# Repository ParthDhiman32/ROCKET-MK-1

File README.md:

# ROCKET-MK-1
This is a fixed fin experimental rocket built for the purpose of collecting useful flight data and also showcasing high level engineering skills 

# Project Theory
For this project I will be designing simulating and fabricating a fixed fin rocket from scratch using the rocket motor as the starting point for calculating all other parameteres like the diameter of the main body tube and the nosecone length and gemoetry and the fin geometry 
the rocket motor's impulse also dictates the maximum weight of the rocket as the thrust to weight ratio should be a minimum of 5:1 considering the resistive forces acting uptom the rocket like the drag from the rocket's weight and also the aerodynamic drag which is the factor which we need to optimize our rocket for we need a very aeroynamically optimized body for the rocket to be able to cut through the air smoothly with minimum drag and deviation 
the rocket should launch perfectly vertical and shall not deviate more then 1-5 degrees from the horizontal from the launch rail The rockst's fins should be optimized to suffer from no Aerosynamic fin flutter.
Aerodynamic Fin Flutter is a destructive process in which the rocket's wings bend under stress and strain as they are travelling at very high speed (upwards of Mach 0.5) for this rocket the fins start to resonate because of the external force which the air provides for stabilizing the rocket but in this special case the air starts to resonate the fin and the fin starts to vibrate from it's mean position which and hench resonate which exposes the fin to much more flutter than it can possibly handel and hence breaks apart.
to avoid this we must use a lightweight material with the highest young's modulus which provided maximum stiffness and negligible strain 
Materials such as Fiberglass, carbon fiber, 3D printed CF-Nylong provide high stiffness ideal for optimizing the fins from restraining from fin flutter 

# Starting parameteres 
Now let's start talking about numbers and actual starting parameteres for the rocket

**Rocket Motor**
Now there are many different classes of rockets ranging from class micro and A going through E F G H I J K L and reaching to upwards of AJ
However for model rocketry we generally use from class D to the largest one S 
These rocket motor classes are alphabetical and classified by Magnitude of impulse they can produce

For my Rocket i will be using a F class rocket motor producing a Max Impulse of 67Ns
I will be using the rocketeers F57 motor 

This motor has 
Diameter of 29mm <br>
Weight = 177g (wet mass)<br>
Burn time = 1.14s<br>

This motor's casing is made from aerospace grade Aluminium 
Nozzel is manufactured out of graphite 
and all very high quality materials are used in this entire rocket motor assembly

# Rocket dimensions
Thr rocket's exact dimenstions are yet to be simulated and found out but for now we have these as the starting points
Rocket length = 650 ~ 975mm<br>
Main Body tube length = 455 ~ 650mm<br>
Avaionics bay length = 120 ~ 165mm<br>
Nose cone length 195 ~ 325mm<br>
Nose cone profile = Ogive (3:1)<br>
Outter tube diameter = 65mm<br>
Target liftoff mass = 500~600 grams<br>
Static stability margin = 1~1.5 cal<br>
3-4 Fixed fins - Trapezoid shape <br>

# Mission Objective 
Apogee > 100 Meteres<br>
Mantain Stable vertical flight <br>
All Flight Data logged successfully <br>
Working Telementry<br>
Rocket Recovery <br>

# Work Flow
Firstly the rough design will be simulated in Open rocket and the simulation data will be used for finding the perfect rocket profile values 

Then the entire rocket will be imported inside fusion 360 and the launch mechanism the launch rail and the cross section of the rocket and the fin joint mechanism and then avaionics bay will also be shown in the horizontal cross section of the rocket 

Then i will prototype the avaionics bay on breadboards and design the rough data logging program and logic This will be a time consuming process 

After this i will convert the entire avaionics circitry into a PCB which will be as small as possible and Be mounted vertically inside the Avaionics bay 

then i will also create the remote ignition and most importantly the ground telementry station which will comminucate via LoRa

After that I will work on creating proper joining mechanisms for the rocket and the final circuitry 

Then i will finalize the rocket design and start ordering parts for it's fabrication and assembly 

Then carefully assemble each and every part and test for any errors 

then calculate the Moment of inertia find the actual center of mass and center of pressure 

Simulate and perfect again in Openrocket 

Then create an even more accurate model in matlab simulink 

Test and analyze again

Then a dry run 

The Actual Flight 

# Avionics <br>
I will be using these main sensors for the avaionics (rough idea)<br>
ESP32 S3 Wroom-1<br>
BMI270 - 3 axis acceleration + 3 axis gyroscope <br>
ADXL377 - 3 axis high G accelerometer<br>
Barometric pressure sensor - altitude measurement<br>
DS3231 - Time stamping<br>
Sd card module - data logging <br>
loRa - Telementry <br>
2 Li-ion battries for Power<br>
umbilical cord connector = communication of Remote ignition from ground station to the rocket and the launch rail <br>

# Launch rail<br>
The launch rail will be made out of 2020 aluminium extrusion with arms which will hold the rocket in place (cool factor) and it will use a Rail button<br>

# OpenRocket model 
*1st Iteration estimates*

Apogee = 285m <br>
Max speed = Mach 0.245<br>
Max acceleration = 83.3m/s^2<br>

*2nd Iteration estimates*

Apogee = 281m<br>
Max speed = Mach 0.240<br>
Max acceleration = 84.6m/s^2 <br>

This version has a more agressive look and also has a much higher stability caliber(2.19Cal) then the last iteration.<br>
I upgraded from a 2020 Aluminium extrusion because a 1010 aluminium extrusion was not very easily available in india.<br>

# Render in fusion360

# Avionics sled V1
<br>
<br>
<br>

# Remote ignition system 

# How to actually build the rocket 
1. Download this repo on your computer
2. Buy all the materials required for the rocket as listed in the BOM
3. Start by taking the carboard main body tube
4. 3D print the nosecone
5. cut the fins out of balsa wood and make insitions inside of the cardboard bodytube for fitting the fins
6. Also cut out the centering rings from the rocket's main body tube
7. Take wood glue and apply it on the centering rings and then slide then at exact depth as mentioned inside the openrocket rocket's model
8. after the centering rings are applied do the same and glue the fins inisde the rocket's main body tube
9. Take the rocket motor and slide it inside the centering rings from the bottom
10. Take the 3d printed nosecone and see if it fits from the top properly
11. make sure it fits tightly enough that it can slip out with force but not when you're lifting the rocket by holding the nosecone
12. Apply tape around the circumfrence of the nose cone's neck if required to a tighter fit
13. after this you may spray a thin layer of primer on the cardboard tube and then spray paint it black
14. Now comes the Avionics
15. Get the Avionics pcb fabricated
16. Solder all the avionics components as shows in the kicad pcb schematics
17. After getting the pcb ready
18. build the ground station on a perf board or a breadboard
19. power up the pcb and the ground station
20. make sure to connect the LoRa antennas before powering on the pcb else it it may fry itself
21. Upload the codes of ther Avionics sender and ground station recuiever respectively
22. Download Serial Studios and open the serial studio profile provided inside the repo
23. Connect the ground station and you should see the serial studio dashboard working
24. After that 3D print the Avionics sled for the Avionics PCB
25. Connect the avionics on the sled via proper M3 screws
26. TAke the sled and slide it inside the rocket's main body tube and then close the nosecone
27. Make sure that the rocket Telementry is working properly
28. Drill a small hole isnide the cardboard tube at the angle bisector between two of the fur fins and connect the rail button
29. Take the 6 Feet 2020 Aluminium extrusion
30. Put it firmly on a tripod stand or a dedicated Launch pad for a model rocket
31. Get the Ignition reciever PCB fabriacted and solder all the components
32. 3D print the acse for the PCB
33. Connecte a 12V Lead acid battery to the ignition bat connector also power the ignition reciever staion with 5V from a smaller battery
34. Connect the igniton plug inside the rocket's motor
35. Now staand atleast 10 meters away from the launch site (make sure you have all the certifications reqired to launch a model rocket according to your local jurisdiction)
36. Load up the Serial studio dashboard
37. Press the launch button o the ground station reciever
38. Rocket launches (hopefully)

# BOM 

| Category | Item Description | Manufacturer / Serial No. / Part Number | Qty | Est. Unit Price (USD) | Primary Vendor / Website |
| :--- | :--- | :--- | :---: | :---: | :--- |
| **Avionics & Processing** | ESP32-S3 Dev Board | Espressif / ESP32-S3-DevKitC-1 | 2 | \$6.50 | [DigiKey](https://www.digikey.com) |
| **Avionics & Processing** | LoRa Transceiver Module (915MHz/433MHz) | HopeRF / RFM95W-915S2 | 2 | \$4.80 | [Adafruit](https://www.adafruit.com) |
| **Avionics & Processing** | 50Ω SMA Male Rubber Duck Antenna | Generic / ANT-SMA-915-01 | 2 | \$2.00 | [Amazon](https://www.amazon.com) |
| **Sensors** | 6-DOF IMU (Gyroscope + Accelerometer) | Bosch / BMI270-BRK | 1 | \$5.50 | [Pimoroni](https://shop.pimoroni.com) |
| **Sensors** | High-G Accelerometer Module | Analog Devices / ADXL345-BRK | 1 | \$4.20 | [SparkFun](https://www.sparkfun.com) |
| **Sensors** | Barometric Pressure & Altitude Sensor | Bosch / BMP280-BRK | 1 | \$3.50 | [Adafruit](https://www.adafruit.com) |
| **Sensors** | 3-Axis Digital Compass / Magnetometer | QST / QMC5883L-MOD | 1 | \$2.50 | [AliExpress](https://www.aliexpress.com) |
| **Sensors** | GPS Receiver Module w/ Ceramic Antenna | u-blox / NEO-6M-0-001 | 1 | \$11.00 | [Amazon](https://www.amazon.com) |
| **Sensors** | Real-Time Clock (RTC) Module | Maxim / DS3231-RTC-MOD | 1 | \$2.80 | [Adafruit](https://www.adafruit.com) |
| **Data & Interfaces** | MicroSD Card Breakout Module (SPI) | Adafruit / ID-254 | 1 | \$1.80 | [Adafruit](https://www.adafruit.com) |
| **Data & Interfaces** | Class 10 MicroSD Card (16GB) | SanDisk / SDSQUNC-016G-GN6MA | 1 | \$7.00 | [Amazon](https://www.amazon.com) |
| **Data & Interfaces** | USB-C High-Speed Data Cable (1m) | Anker / A81E1011 | 2 | \$3.00 | [Monoprice](https://www.monoprice.com) |
| **Power & Passives** | 3.7V 1S LiPo Battery (1000mAh 25C) | Turnigy / N1000.1S.25 | 1 | \$6.50 | [HobbyKing](https://hobbyking.com) |
| **Power & Passives** | TP4056 LiPo Charge/Protection Module | Micro-USB TP4056-PROT | 1 | \$0.80 | [AliExpress](https://www.aliexpress.com) |
| **Power & Passives** | 3.3V Low Dropout LDO Regulator | Advanced Monolithic / AMS1117-3.3 | 2 | \$0.40 | [DigiKey](https://www.digikey.com) |
| **Power & Passives** | Ceramic Capacitor 0.1uF 50V (0805/DIP) | KEMET / C0805C104K5RACTU | 10 | \$0.05 | [Mouser](https://www.mouser.com) |
| **Power & Passives** | Tantalum Capacitor 10uF 16V | AVX / TAJB106K016RNJ | 4 | \$0.25 | [Mouser](https://www.mouser.com) |
| **Power & Passives** | Resistor Kit (2.2kΩ, 4.7kΩ, 10kΩ, 220Ω) | Yageo / MFR-25FRF52 Series | 1 set | \$5.00 | [Amazon](https://www.amazon.com) |
| **Airframe & Hardware** | Spiral Wound Cardboard Tube (62mm ID) | Apogee Components / Tubing-62mm | 1m | \$12.00 | [Apogee Components](https://www.apogeerockets.com) |
| **Airframe & Hardware** | Airframe Coupler Tube (62mm ID Fit) | Apogee Components / Coupler-62mm | 1 | \$5.00 | [Apogee Components](https://www.apogeerockets.com) |
| **Airframe & Hardware** | PETG Filament 1.75mm (Sled Printing) | Prusametrix / PETG-JET-BLACK | 1 | \$22.00 | [Prusa Research](https://www.prusa3d.com) |
| **Airframe & Hardware** | M4 Threaded Rods Stainless Steel (300mm) | McMaster-Carr / 98846A029 | 2 | \$2.50 | [McMaster-Carr](https://www.mcmaster.com) |
| **Airframe & Hardware** | M3 x 5mm x 4.2mm Brass Heat-Set Inserts | McMaster-Carr / 94180A331 | 8 | \$0.20 | [McMaster-Carr](https://www.mcmaster.com) |
| **Airframe & Hardware** | Birch Plywood Centering Rings (62mm OD) | Custom Laser / CR-62-3MM | 3 | \$2.00 | Local Laser Cutting |
| **GCS & Countdown** | Heavy Duty Toggle Switch w/ Safety Cover | Gardner Bender / GSW-11 | 5 | \$1.50 | [Amazon](https://www.amazon.com) |
| **GCS & Countdown** | Momentary Red E-Stop Push Button Switch | Ideal / Push-Red-Mushroom-22mm | 1 | \$3.50 | [AliExpress](https://www.aliexpress.com) |
| **GCS & Countdown** | PAM8403 Audio Amplifier Module | Mini PAM8403-2CH-3W | 1 | \$1.20 | [AliExpress](https://www.aliexpress.com) |
| **GCS & Countdown** | 8Ω 2W Mini Speaker Module | CUI Devices / CMS-151185-078SP | 1 | \$1.50 | [DigiKey](https://www.digikey.com) |
| **GCS & Countdown** | 1-Channel 5V Optocoupler Relay Module | Songle / SRD-05VDC-SL-C | 1 | \$1.00 | [Amazon](https://www.amazon.com) |

*Total Estimated Project Cost: **~$135.00 USD***

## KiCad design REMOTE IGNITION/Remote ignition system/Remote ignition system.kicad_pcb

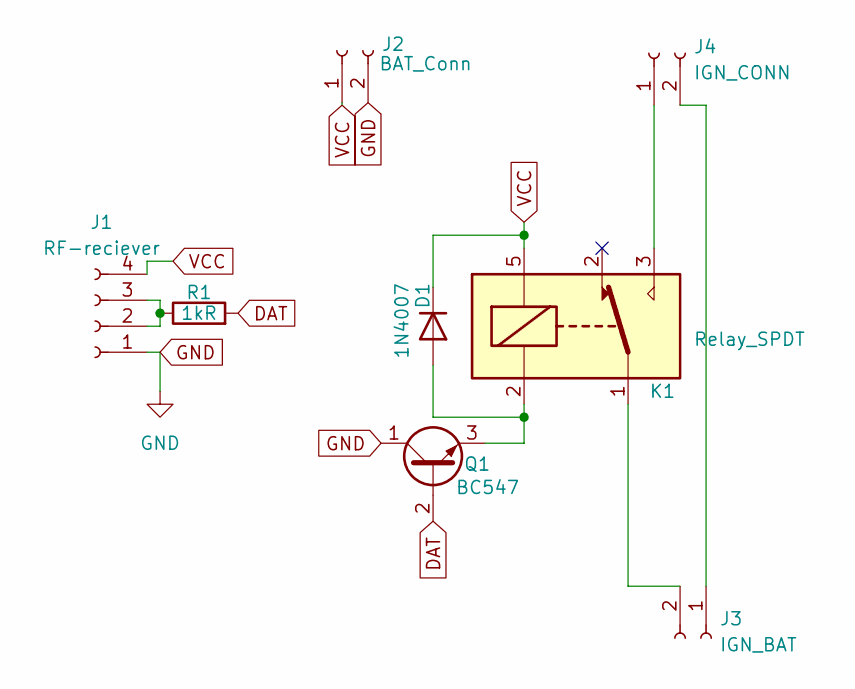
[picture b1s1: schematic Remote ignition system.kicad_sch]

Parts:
D1: 1N4007; D_DO-41_SOD81_P10.16mm_Horizontal
J1: RF-reciever; PinHeader_1x04_P2.54mm_Vertical
J2: BAT_Conn; TerminalBlock_Phoenix_MKDS-1,5-2-5.08_1x02_P5.08mm_Horizont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
J3: IGN_BAT; TerminalBlock_Phoenix_MKDS-1,5-2-5.08_1x02_P5.08mm_Horizont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
J4: IGN_CONN; TerminalBlock_Phoenix_MKDS-1,5-2-5.08_1x02_P5.08mm_Horizont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
K1: Relay_SPDT; Relay_SPDT_SANYOU_SRD_Series_Form_C
Q1: BC547; TO-92_Inline
R1: 1kR; R_Axial_DIN0207_L6.3mm_D2.5mm_P7.62mm_Horizontal

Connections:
DAT: Q1.2 (B), R1.2
GND: J1.1, J2.2, Q1.1 (C)
unnamed: D1.2 (A), K1.2 (A2), Q1.3 (E)
unnamed: J1.2, J1.3, R1.1
unnamed: J3.1, J4.2
unnamed: J3.2, K1.1
unnamed: J4.1, K1.3 (14)
VCC: D1.1 (K), J1.4, J2.1, K1.5 (A1)

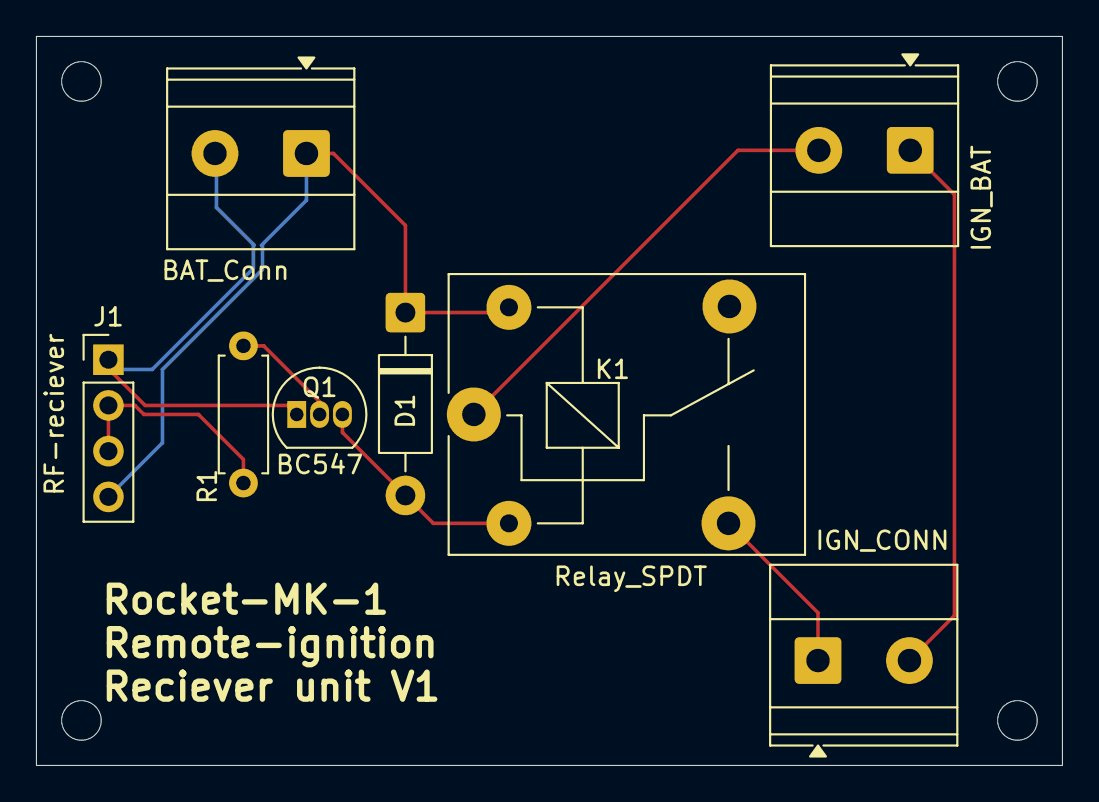
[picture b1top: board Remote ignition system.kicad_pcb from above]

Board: 2 copper layers, 57.0 x 40.5 mm, 8 parts (0 on the bottom side), 8 nets.

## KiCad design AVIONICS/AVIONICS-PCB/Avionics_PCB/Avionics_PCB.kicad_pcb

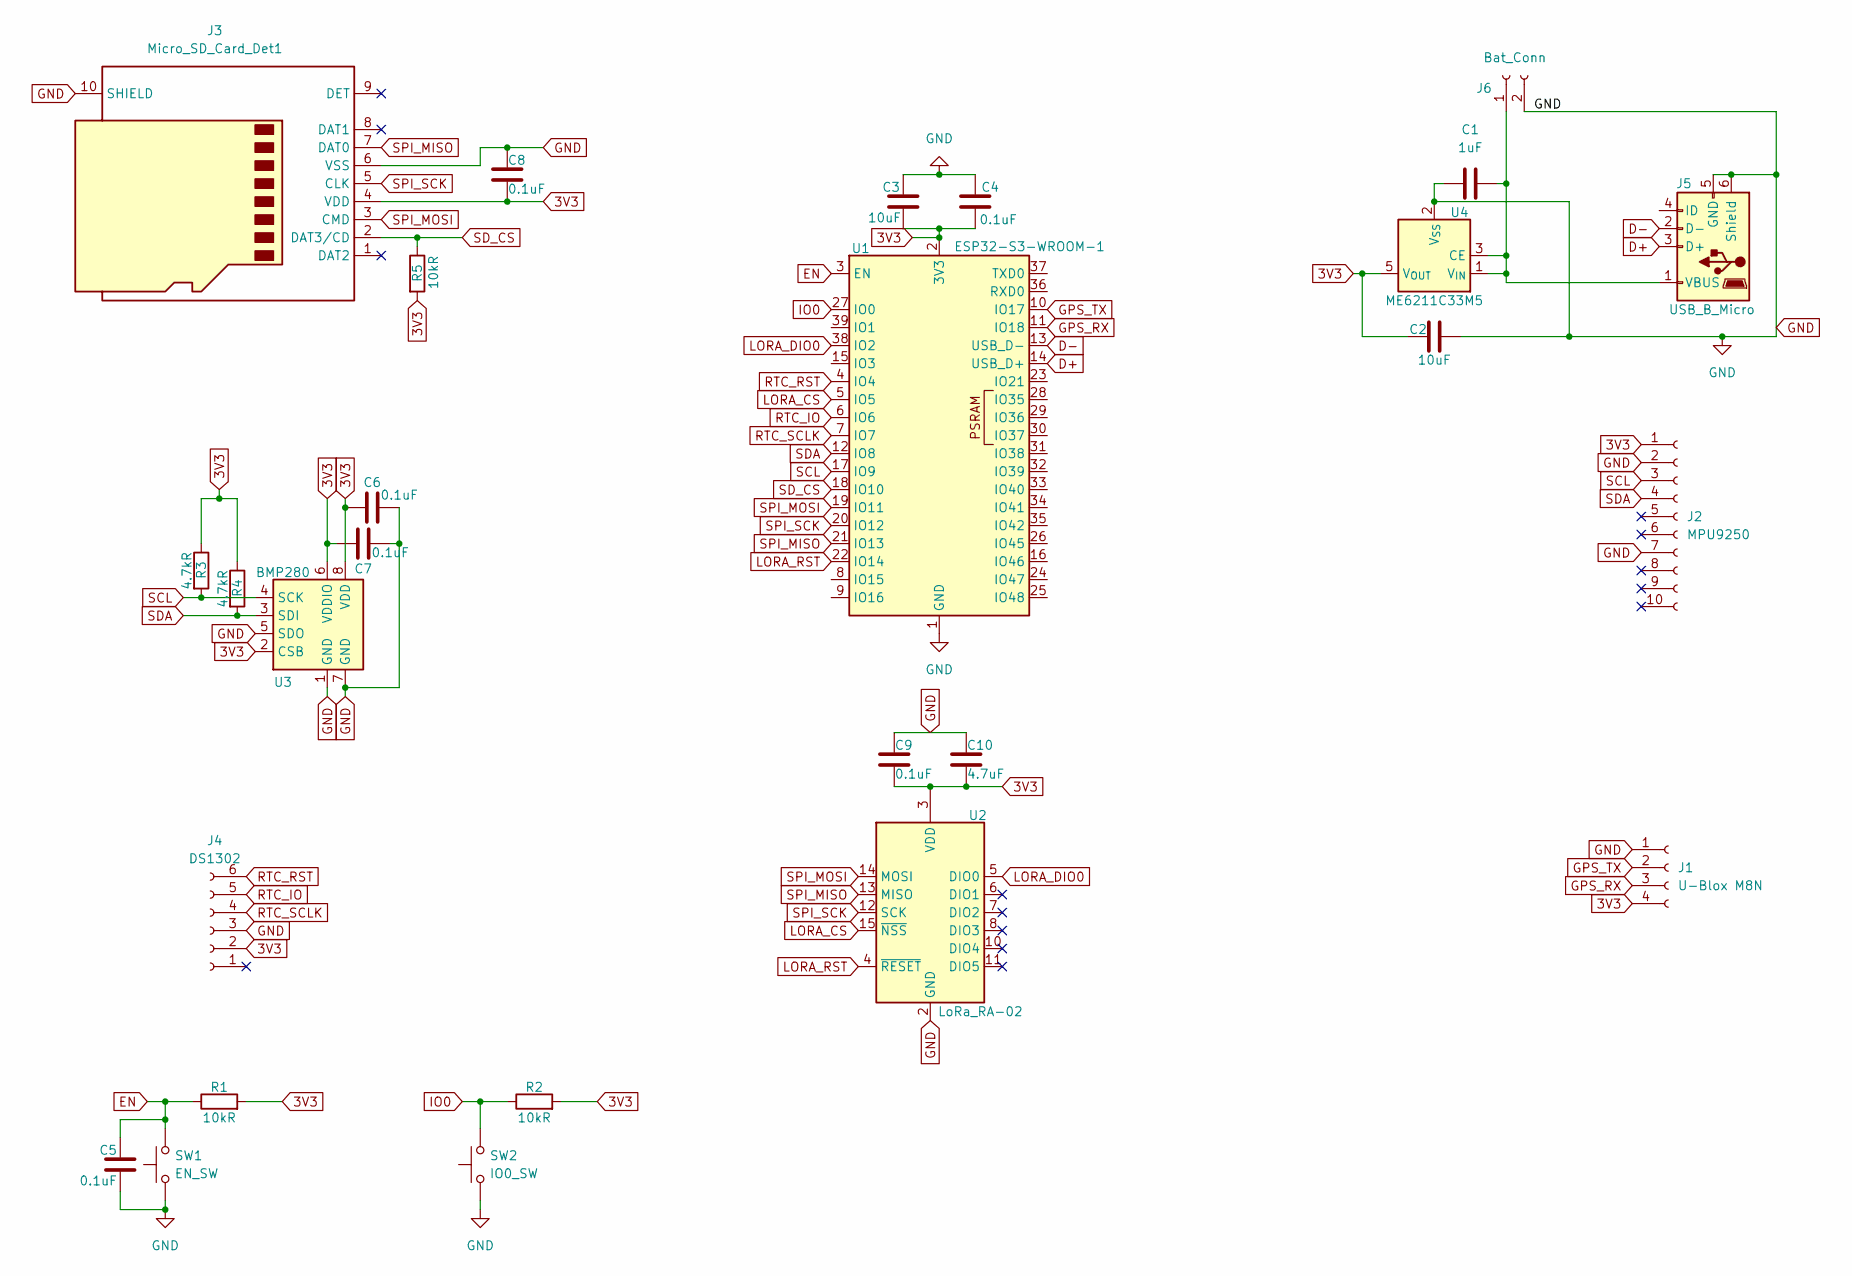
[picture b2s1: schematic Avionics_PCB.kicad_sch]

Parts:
C1: 1uF; C_0805_2012Metric
C2, C3: 10uF; C_0805_2012Metric
C4, C5, C6, C7, C8, C9: 0.1uF; C_0805_2012Metric
C10: 4.7uF; C_0805_2012Metric
J1: U-Blox M8N; PinHeader_1x04_P2.54mm_Vertical
J2: MPU9250; PinHeader_1x10_P2.54mm_Vertical
J3: Micro_SD_Card_Det1; microSD_HC_Hirose_DM3AT-SF-PEJM5
J4: DS1302; PinHeader_1x06_P2.54mm_Vertical
J5: USB_B_Micro; USB_Micro-B_Molex-105017-0001
J6: Bat_Conn; JST_PH_B2B-PH-K_1x02_P2.00mm_Vertical
R1, R2, R5: 10kR; R_0805_2012Metric
R3, R4: 4.7kR; R_0805_2012Metric
SW1: EN_SW; SW_Tactile_Straight_KSA0Axx1LFTR
SW2: IO0_SW; SW_Tactile_Straight_KSA0Axx1LFTR
U1: ESP32-S3-WROOM-1
U2: LoRa_RA-02; Ai-Thinker-Ra-01-LoRa
U3: BMP280; Bosch_LGA-8_2x2.5mm_P0.65mm_ClockwisePinNumbering
U4: ME6211C33M5; SOT-23-5

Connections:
3V3: C2.1, C3.2, C4.2, C6.1, C7.1, C8.2, C9.2, C10.2, J1.4, J2.1, J3.4 (VDD), J4.2, R1.2, R2.2, R3.1, R4.1, R5.2, U1.2 (3V3), U2.3 (VDD), U3.2 (CSB), U3.6 (VDDIO), U3.8 (VDD), U4.5 (V_{OUT})
D+: J5.3 (D+), U1.14 (USB_D+)
D-: J5.2 (D-), U1.13 (USB_D-)
EN: C5.1, R1.1, SW1.2, U1.3 (EN)
GND: C1.1, C2.2, C3.1, C4.1, C5.2, C6.2, C7.2, C8.1, C9.1, C10.1, J1.1, J2.2, J2.7, J3.6 (VSS), J3.10 (SHIELD), J4.3, J5.5 (GND), J5.6 (Shield), J6.2, SW1.1, SW2.1, U1.1 (GND), U1.40 (GND), U1.41 (GND), U2.1 (GND), U2.2 (GND), U2.9 (GND), U2.16 (GND), U3.1 (GND), U3.5 (SDO), U3.7 (GND), U4.2 (V_{SS})
GPS_RX: J1.3, U1.11 (IO18)
GPS_TX: J1.2, U1.10 (IO17)
IO0: R2.1, SW2.2, U1.27 (IO0)
LORA_CS: U1.5 (IO5), U2.15 (~NSS)
LORA_DIO0: U1.38 (IO2), U2.5 (DIO0)
LORA_RST: U1.22 (IO14), U2.4 (~RESET)
unnamed: C1.2, J5.1 (VBUS), J6.1, U4.1 (V_{IN}), U4.3 (CE)
RTC_IO: J4.5, U1.6 (IO6)
RTC_RST: J4.6, U1.4 (IO4)
RTC_SCLK: J4.4, U1.7 (IO7)
SCL: J2.3, R3.2, U1.17 (IO9), U3.4 (SCK)
SDA: J2.4, R4.2, U1.12 (IO8), U3.3 (SDI)
SD_CS: J3.2 (DAT3/CD), R5.1, U1.18 (IO10)
SPI_MISO: J3.7 (DAT0), U1.21 (IO13), U2.13 (MISO)
SPI_MOSI: J3.3 (CMD), U1.19 (IO11), U2.14 (MOSI)
SPI_SCK: J3.5 (CLK), U1.20 (IO12), U2.12 (SCK)

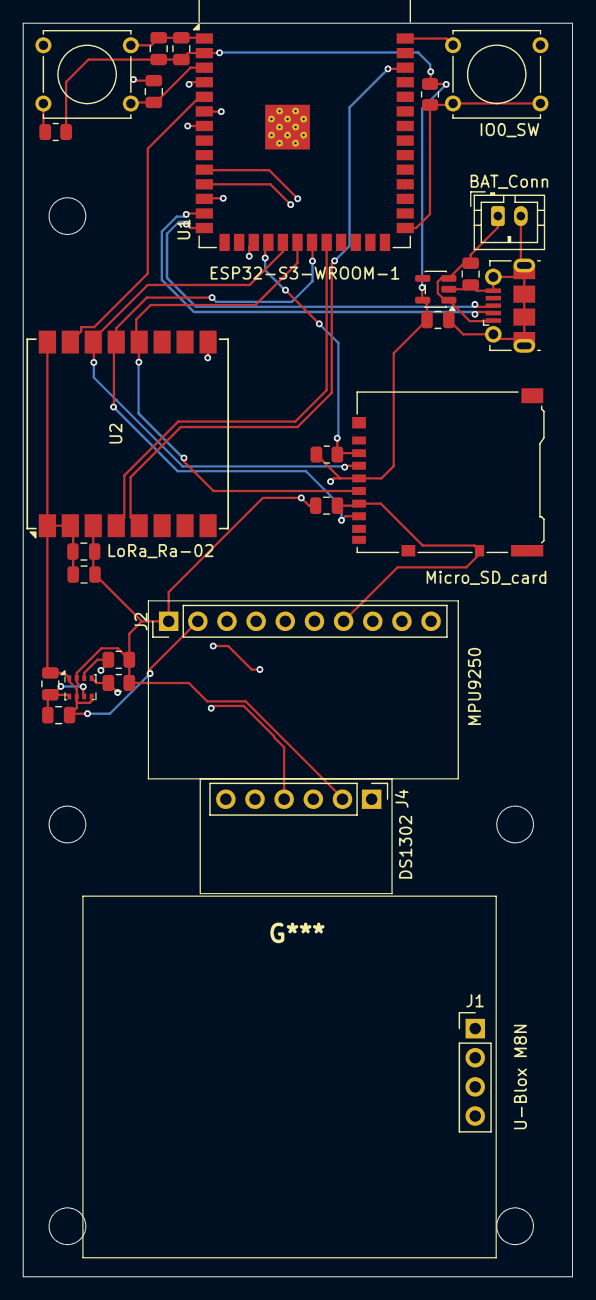
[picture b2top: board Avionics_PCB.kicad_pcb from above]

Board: 4 copper layers, 47.8 x 109.2 mm, 27 parts (0 on the bottom side), 21 nets.

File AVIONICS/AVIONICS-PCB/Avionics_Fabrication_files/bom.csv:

Designator,Footprint,Quantity,Value,LCSC Part #
C1,0805,1,1uF,
C10,0805,1,4.7uF,
"C2, C3",0805,2,10uF,
"C4, C5, C6, C7, C8, C9",0805,6,0.1uF,
J1,PinHeader_1x04_P2.54mm_Vertical,1,U-Blox M8N,
J2,PinHeader_1x10_P2.54mm_Vertical,1,MPU9250,
J3,microSD_HC_Hirose_DM3AT-SF-PEJM5,1,Micro_SD_card,
J4,PinHeader_1x06_P2.54mm_Vertical,1,DS1302,
J5,USB_Micro-B_Molex-105017-0001,1,USB_B_Micro,
J6,JST_PH_B2B-PH-K_1x02_P2.00mm_Vertical,1,Bat_Conn,
"R1, R2, R5",0805,3,10kR,
"R3, R4",0805,2,4.7kR,
SW1,SW_Tactile_Straight_KSA0Axx1LFTR,1,EN_SW,
SW2,SW_Tactile_Straight_KSA0Axx1LFTR,1,IO0_SW,
U1,ESP32-S3-WROOM-1,1,ESP32-S3-WROOM-1,
U2,Ai-Thinker-Ra-01-LoRa,1,LoRa_Ra-02,
U3,Bosch_LGA-8_2x2.5mm_P0.65mm_ClockwisePinNumbering,1,BMP280,
U4,SOT-23-5,1,ME6211C33M5,

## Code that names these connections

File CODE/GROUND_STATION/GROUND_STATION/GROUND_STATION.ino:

#include <SPI.h>
#include <LoRa.h>
#include <AudioFileSourcePROGMEM.h>
#include <AudioGeneratorMP3.h>
#include <AudioOutputI2S.h> // Reverted back to the standard library I2S output

#define LORA_CS_PIN   5
#define LORA_RST_PIN  14
#define LORA_DIO0_PIN 2

// --- INCLUDE YOUR 2 CONVERTED MP3 HEADER FILES ---
#include "out_of_trajectory.h"    
#include "hard_deceleration.h"    

// Audio pipeline objects
AudioGeneratorMP3 *mp3;
AudioFileSourcePROGMEM *file;
AudioOutputI2S *out;

// Mission State tracking
int missionState = 1;
int previousMissionState = -1;

// Simulation timer variables (switches state every 3 seconds for testing)
unsigned long lastSimTime = 0;
const unsigned long simInterval = 3000; 

void setup() {
  Serial.begin(115200);
  while (!Serial);
  delay(1000);

  Serial.println("\n=== ROCKET MK-1 GROUND STATION: DUAL-WARNING MP3 AUDIO ===");

  // Initialize I2S Audio Output (BCLK: 26, LRC: 25, DIN: 22)
  out = new AudioOutputI2S();
  out->SetGain(0.85); // Volume level (0.0 to 1.0)
  out->SetPinout(26, 25, 22); 

  mp3 = new AudioGeneratorMP3();

  // Initialize LoRa
  LoRa.setPins(LORA_CS_PIN, LORA_RST_PIN, LORA_DIO0_PIN);
  if (!LoRa.begin(433E6)) {
    Serial.println("[LoRa FAILED] Check antenna! (Running simulation loop)");
  } else {
    Serial.println("[LoRa SUCCESS]");
  }

  // Must match sender radio configuration exactly
  LoRa.setSyncWord(0xF3);
  LoRa.setSignalBandwidth(500E3);
  LoRa.setSpreadingFactor(7);
  LoRa.setCodingRate4(5);
}

// Function to trigger warning MP3s based on state
void playWarningMP3(int state) {
  // Stop any currently playing audio stream
  if (mp3->isRunning()) {
    mp3->stop();
  }

  const uint8_t *audioData = nullptr;
  uint32_t audioLen = 0;

  // Map state 5 and state 6 to their respective header arrays
  if (state == 5) {
    audioData = out_of_trajectory_mp3;
    audioLen = out_of_trajectory_len;
    Serial.println("[AUDIO] Playing: Out of Trajectory Warning");
  } 
  else if (state == 6) {
    audioData = hard_deceleration_mp3;
    audioLen = hard_deceleration_len;
    Serial.println("[AUDIO] Playing: Hard Deceleration Warning");
  }

  // If a valid warning audio file was selected, start playback
  if (audioData != nullptr && audioLen > 0) {
    file = new AudioFileSourcePROGMEM(audioData, audioLen);
    mp3->begin(file, out);
  }
}

void loop() {
  // 1. CRITICAL: Keep the MP3 decoder pumping data in the background non-stop
  if (mp3->isRunning()) {
    if (!mp3->loop()) {
      mp3->stop();
    }
  }

  // 2. Non-blocking state sweep timer (advances state every 3 seconds for testing)
  if (millis() - lastSimTime >= simInterval) {
    lastSimTime = millis();
    missionState++;
    if (missionState > 10) missionState = 1; // Loops back to 1
  }

  // 3. State Transition Audio Trigger Check (Fires ONCE when entering State 5 or 6)
  if (missionState != previousMissionState) {
    previousMissionState = missionState;
    playWarningMP3(missionState);
  }

  // 4. Telemetry Stream: Sends sensor string + integer state at index 19 to Serial Studio
  static unsigned long lastStreamTime = 0;
  if (millis() - lastStreamTime >= 1000) { // Stream every 1 second
    lastStreamTime = millis();

    String sensorPayload = "101,18:26:41,00:00:00,0.0,0.0,0.0,0.0,0.29,5.95,0.30,38,98835.20,209.39,-1.69,-0.13,9.50,-0.00,-0.03,-0.01";
    
    Serial.print("$");
    Serial.print(sensorPayload);
    Serial.print(",");
    Serial.println(missionState);
  }

  // 5. Real LoRa Packet Handling (Appends current state integer to live incoming packets)
  int packetSize = LoRa.parsePacket();
  if (packetSize) {
    String incomingPacket = "";
    while (LoRa.available()) {
      incomingPacket += (char)LoRa.read();
    }
    incomingPacket.trim();
    if (incomingPacket.startsWith("$")) incomingPacket = incomingPacket.substring(1);

    Serial.print("$");
    Serial.print(incomingPacket);
    Serial.print(",");
    Serial.println(missionState);
  }
}
